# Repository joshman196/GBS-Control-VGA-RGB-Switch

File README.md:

# VGA-RGB Switch for the GBS Control
A very simple PCB containing a 100-ohm resistor and a switch to toggle between VGA and "TV" RGB (75-ohm termination). Comes in surface mount and through hole styles.

**Note:** The current wording of the switch says "off" and "on" because I originally named it a VGA switch, but this is technically a flawed way of looking at it. In this case, just be aware that "off" means TV RGB (75-ohm termination) and "on" means VGA (like with Dreamcast VGA output or otherwise). I may eventually change this, but I had this sitting on my drive for almost three years and just wanted to make it public already.

Wiring is shown in the last picture below, although you can alternatively wire the top right pad to the big ground pin next to the VGA input, as well as wiring the top left pad to the big "S"/Sync pin next to the VGA input.

## Parts Needed
- A 100-ohm resistor, 0805 size for surface mount
- SPST switch, I used one of [these](https://www.aliexpress.us/item/2255800031738457.html?gatewayAdapt=glo2usa4itemAdapt)

### Surface Mount PCB

### Through Hole PCB (Untested)

### Pictures

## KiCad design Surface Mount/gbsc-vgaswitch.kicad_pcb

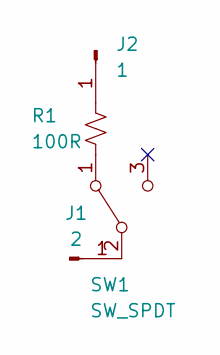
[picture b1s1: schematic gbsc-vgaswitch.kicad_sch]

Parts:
J1: 2; TestPoint_Pad_2.0x2.0mm
J2: 1; TestPoint_Pad_2.0x2.0mm
R1: 100R; R_0805_2012Metric_Pad1.20x1.40mm_HandSolder
SW1: SW_SPDT; SW_Slide_SPDT_Angled_CK_OS102011MA1Q

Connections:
unnamed: J1.1, SW1.2 (B)
unnamed: J2.1, R1.1
unnamed: R1.2, SW1.1 (A)

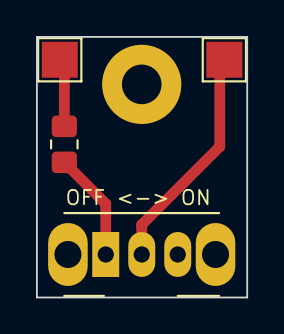
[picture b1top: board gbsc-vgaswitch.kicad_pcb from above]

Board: 2 copper layers, 11.7 x 14.5 mm, 4 parts (0 on the bottom side), 3 nets.

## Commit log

2026-02-12 main files
